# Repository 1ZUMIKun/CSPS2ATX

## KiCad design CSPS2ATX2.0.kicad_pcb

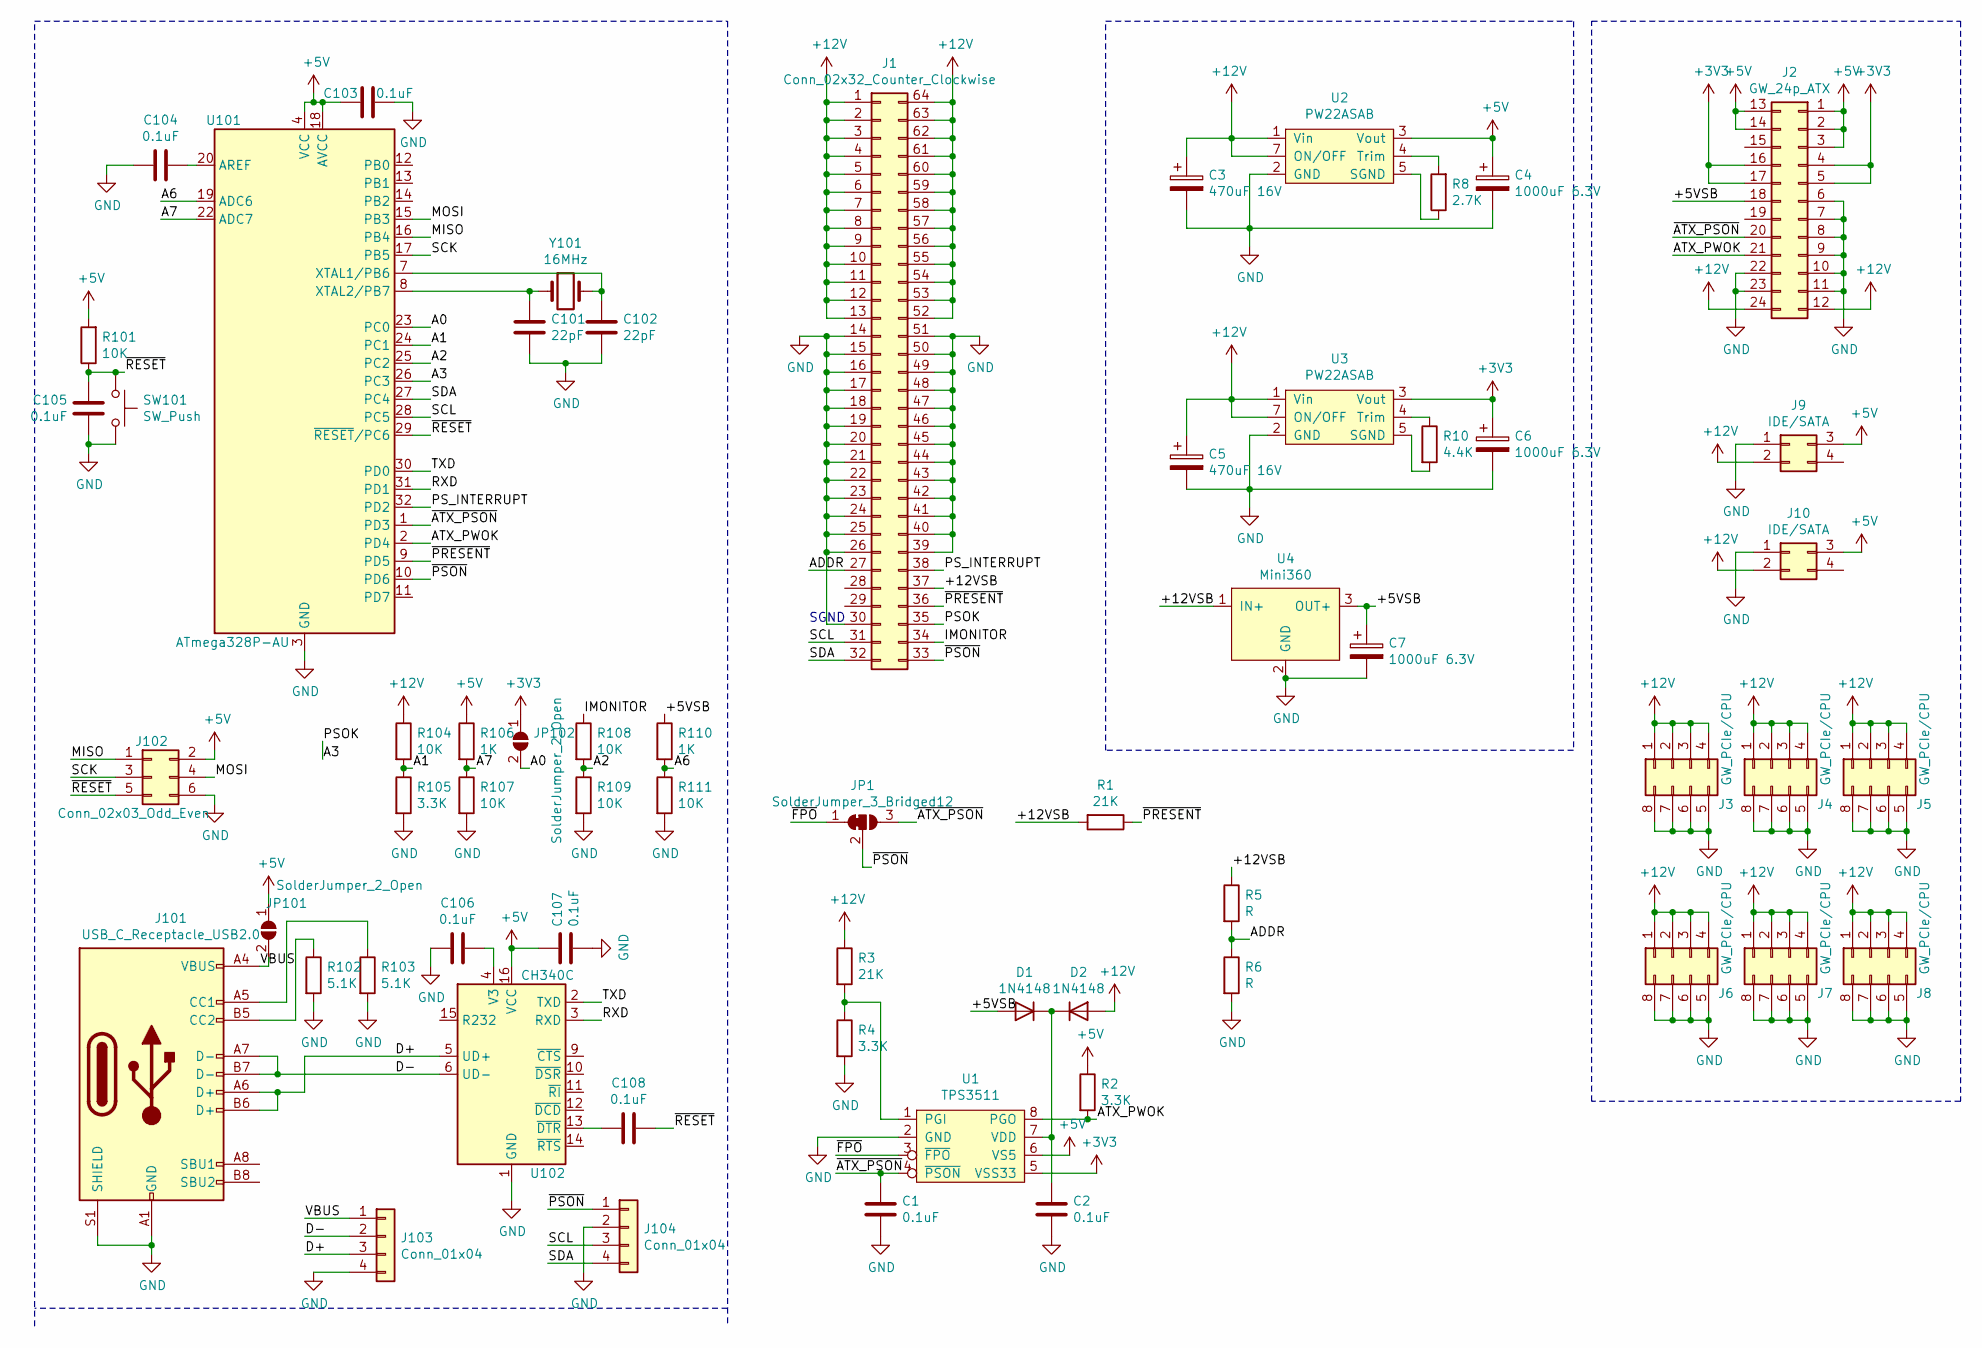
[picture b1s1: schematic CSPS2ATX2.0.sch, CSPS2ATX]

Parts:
C1, C2, C103, C104, C105, C106, C107, C108: 0.1uF; C_0805_2012Metric
C3, C5: 470uF 16V; CP_Elec_8x10
C4, C6, C7: 1000uF 6.3V; CP_Elec_8x10
C101, C102: 22pF; C_0805_2012Metric
D1, D2: 1N4148; D_SOD-523
J1: Conn_02x32_Counter_Clockwise; CSPS_64P_2.54mm
J2: GW_24p_ATX; ATX_24Pin_P4.20mm_Vertical_4.20mm
J3, J4, J5, J6, J7, J8: GW_PCIe/CPU; ATX_8Pin_P4.20mm_Vertical_4.20mm
J9, J10: IDE/SATA; ATX_4Pin_P4.20mm_Vertical_4.20mm
J101: USB_C_Receptacle_USB2.0; USB_C_Receptacle_Palconn_UTC16-G
J102: Conn_02x03_Odd_Even; PinHeader_2x03_P2.54mm_Vertical
J103, J104: Conn_01x04; PinHeader_1x04_P2.54mm_Vertical
JP1: SolderJumper_3_Bridged12; SolderJumper-3_P1.3mm_Bridged12_RoundedPad1.0x1.5mm
JP101, JP102: SolderJumper_2_Open; SolderJumper-2_P1.3mm_Open_RoundedPad1.0x1.5mm
R1, R3: 21K; R_0805_2012Metric
R2, R4, R105: 3.3K; R_0805_2012Metric
R5, R6: R; R_0805_2012Metric
R8: 2.7K; R_0805_2012Metric
R10: 4.4K; R_0805_2012Metric
R101, R104, R107, R108, R109, R111: 10K; R_0805_2012Metric
R102, R103: 5.1K; R_0805_2012Metric
R106, R110: 1K; R_0805_2012Metric
SW101: SW_Push; SW_SPST_FSMSM
U1: TPS3511; SOIC-8_3.9x4.9mm_P1.27mm
U2, U3: PW22ASAB
U4: Mini360
U101: ATmega328P-AU; TQFP-32_7x7mm_P0.8mm
U102: CH340C; SOIC-16_3.9x9.9mm_P1.27mm
Y101: 16MHz; Crystal_SMD_5032-2Pin_5.0x3.2mm

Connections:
+3V3: C6.1, J2.4, J2.5, J2.16, J2.17, JP102.1 (A), U1.5 (VSS33), U3.3 (Vout)
+5V: C4.1, C103.2, C107.1, J2.1, J2.2, J2.3, J2.13, J2.14, J9.3, J10.3, J102.2, JP101.1 (A), R2.1, R101.2, R106.1, U1.6 (VS5), U2.3 (Vout), U101.4 (VCC), U101.6 (VCC), U101.18 (AVCC), U102.16 (VCC)
+12V: C3.1, C5.1, D2.2 (A), J1.1, J1.2, J1.3, J1.4, J1.5, J1.6, J1.7, J1.8, J1.9, J1.10, J1.11, J1.12, J1.13, J1.52, J1.53, J1.54, J1.55, J1.56, J1.57, J1.58, J1.59, J1.60, J1.61, J1.62, J1.63, J1.64, J2.12, J2.24, J3.1, J3.2, J3.3, J3.4, J4.1, J4.2, J4.3, J4.4, J5.1, J5.2, J5.3, J5.4, J6.1, J6.2, J6.3, J6.4, J7.1, J7.2, J7.3, J7.4, J8.1, J8.2, J8.3, J8.4, J9.2, J10.2, R3.1, R104.1, U2.1 (Vin), U2.7 (ON/OFF), U3.1 (Vin), U3.7 (ON/OFF)
/+5VSB: C7.1, D1.2 (A), J2.18, R110.1, U4.3 (OUT+)
/+12VSB: J1.37, R1.2, R5.1, U4.1 (IN+)
/A0: JP102.2 (B), U101.23 (PC0)
/A1: R104.2, R105.1, U101.24 (PC1)
/A2: R108.2, R109.1, U101.25 (PC2)
/A3: J1.35, U101.26 (PC3)
/A6: R110.2, R111.1, U101.19 (ADC6)
/A7: R106.2, R107.1, U101.22 (ADC7)
/ADDR: J1.27, R5.2, R6.1
/ATX_PWOK: J2.21, R2.2, U1.8 (PGO), U101.2 (PD4)
/D+: J101.A6 (D+), J101.B6 (D+), J103.3, U102.5 (UD+)
/D-: J101.A7 (D-), J101.B7 (D-), J103.2, U102.6 (UD-)
/IMONITOR: J1.34, R108.1
/MISO: J102.1, U101.16 (PB4)
/MOSI: J102.4, U101.15 (PB3)
/PS_INTERRUPT: J1.38, U101.32 (PD2)
/RXD: U101.31 (PD1), U102.3 (RXD)
/SCK: J102.3, U101.17 (PB5)
/SCL: J1.31, J104.3, U101.28 (PC5)
/SDA: J1.32, J104.4, U101.27 (PC4)
/TXD: U101.30 (PD0), U102.2 (TXD)
/VBUS: J101.A4 (VBUS), J101.A9 (VBUS), J101.B4 (VBUS), J101.B9 (VBUS), J103.1, JP101.2 (B)
/~ATX_PSON: C1.1, J2.20, JP1.3 (B), U1.4 (~PSON), U101.1 (PD3)
/~FPO: JP1.1 (A), U1.3 (~FPO)
/~PRESENT: J1.36, R1.1, U101.9 (PD5)
/~PSON: J1.33, J104.1, JP1.2 (C), U101.10 (PD6)
/~RESET: C105.2, C108.2, J102.5, R101.1, SW101.1, U101.29 (~RESET~/PC6)
GND: C1.2, C2.2, C3.2, C4.2, C5.2, C6.2, C7.2, C101.2, C102.2, C103.1, C104.1, C105.1, C106.2, C107.2, J1.14, J1.15, J1.16, J1.17, J1.18, J1.19, J1.20, J1.21, J1.22, J1.23, J1.24, J1.25, J1.26, J1.30, J1.39, J1.40, J1.41, J1.42, J1.43, J1.44, J1.45, J1.46, J1.47, J1.48, J1.49, J1.50, J1.51, J2.6, J2.7, J2.8, J2.9, J2.10, J2.11, J2.22, J2.23, J3.5, J3.6, J3.7, J3.8, J4.5, J4.6, J4.7, J4.8, J5.5, J5.6, J5.7, J5.8, J6.5, J6.6, J6.7, J6.8, J7.5, J7.6, J7.7, J7.8, J8.5, J8.6, J8.7, J8.8, J9.1, J10.1, J101.A1 (GND), J101.A12 (GND), J101.B1 (GND), J101.B12 (GND), J101.S1 (SHIELD), J102.6, J103.4, J104.2, R4.2, R6.2, R102.2, R103.2, R105.2, R107.2, R109.2, R111.2, SW101.2, U1.2 (GND), U2.2 (GND), U3.2 (GND), U4.2 (GND), U101.3 (GND), U101.5 (GND), U101.21 (GND), U102.1 (GND)
unnamed: C2.1, D1.1 (K), D2.1 (K), U1.7 (VDD)
unnamed: C101.1, U101.8 (XTAL2/PB7), Y101.1
unnamed: C102.1, U101.7 (XTAL1/PB6), Y101.2
unnamed: C104.2, U101.20 (AREF)
unnamed: C106.1, U102.4 (V3)
unnamed: C108.1, U102.13 (~DTR)
unnamed: J101.A5 (CC1), R103.1
unnamed: J101.B5 (CC2), R102.1
unnamed: R3.2, R4.1, U1.1 (PGI)
unnamed: R8.1, U2.5 (SGND)
unnamed: R8.2, U2.4 (Trim)
unnamed: R10.1, U3.4 (Trim)
unnamed: R10.2, U3.5 (SGND)

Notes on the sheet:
SGND

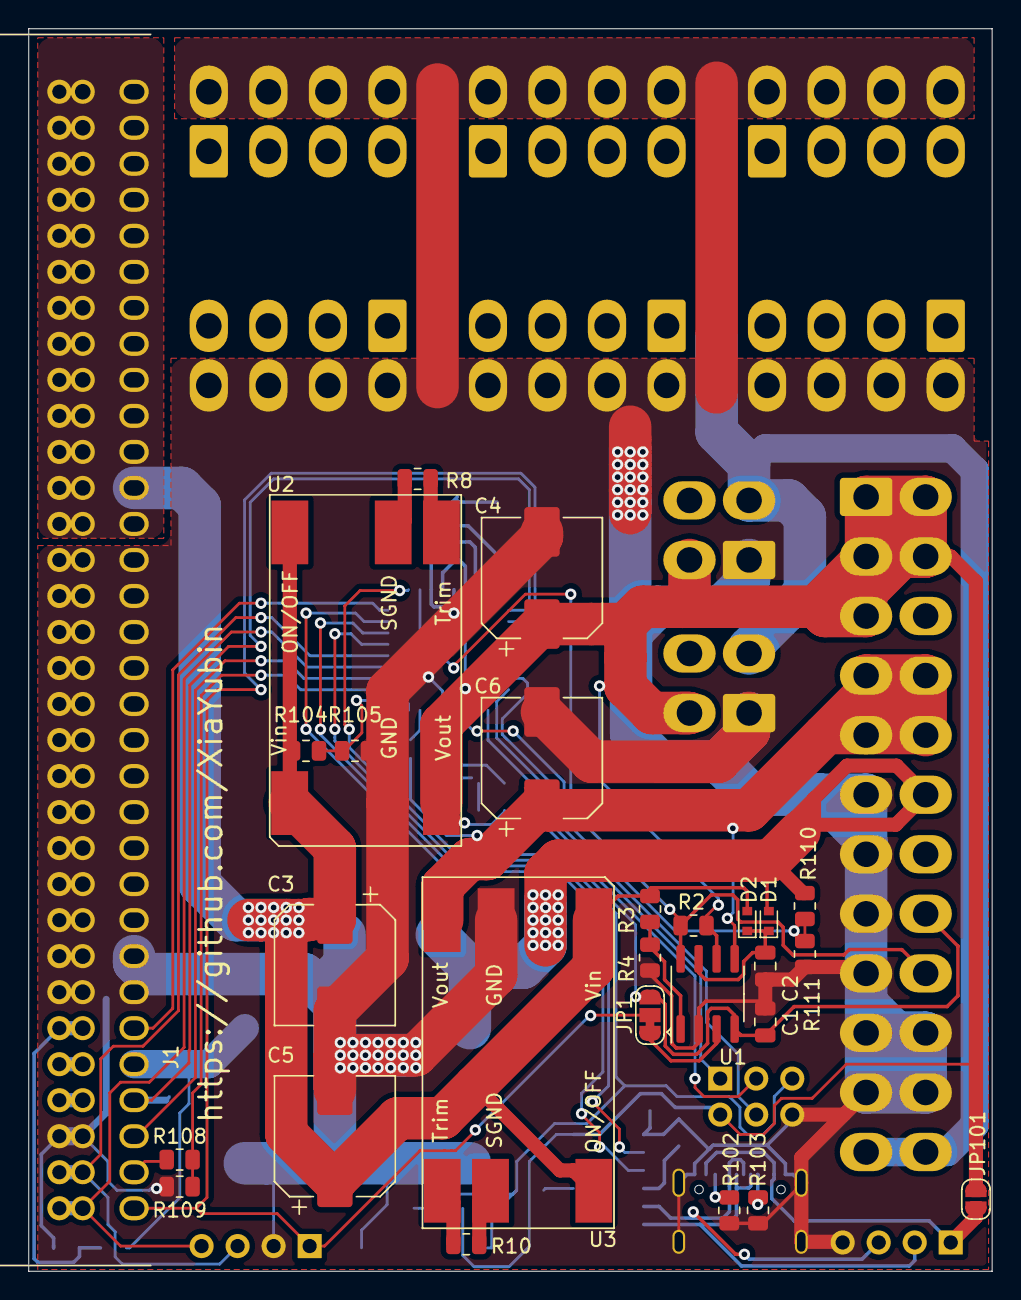
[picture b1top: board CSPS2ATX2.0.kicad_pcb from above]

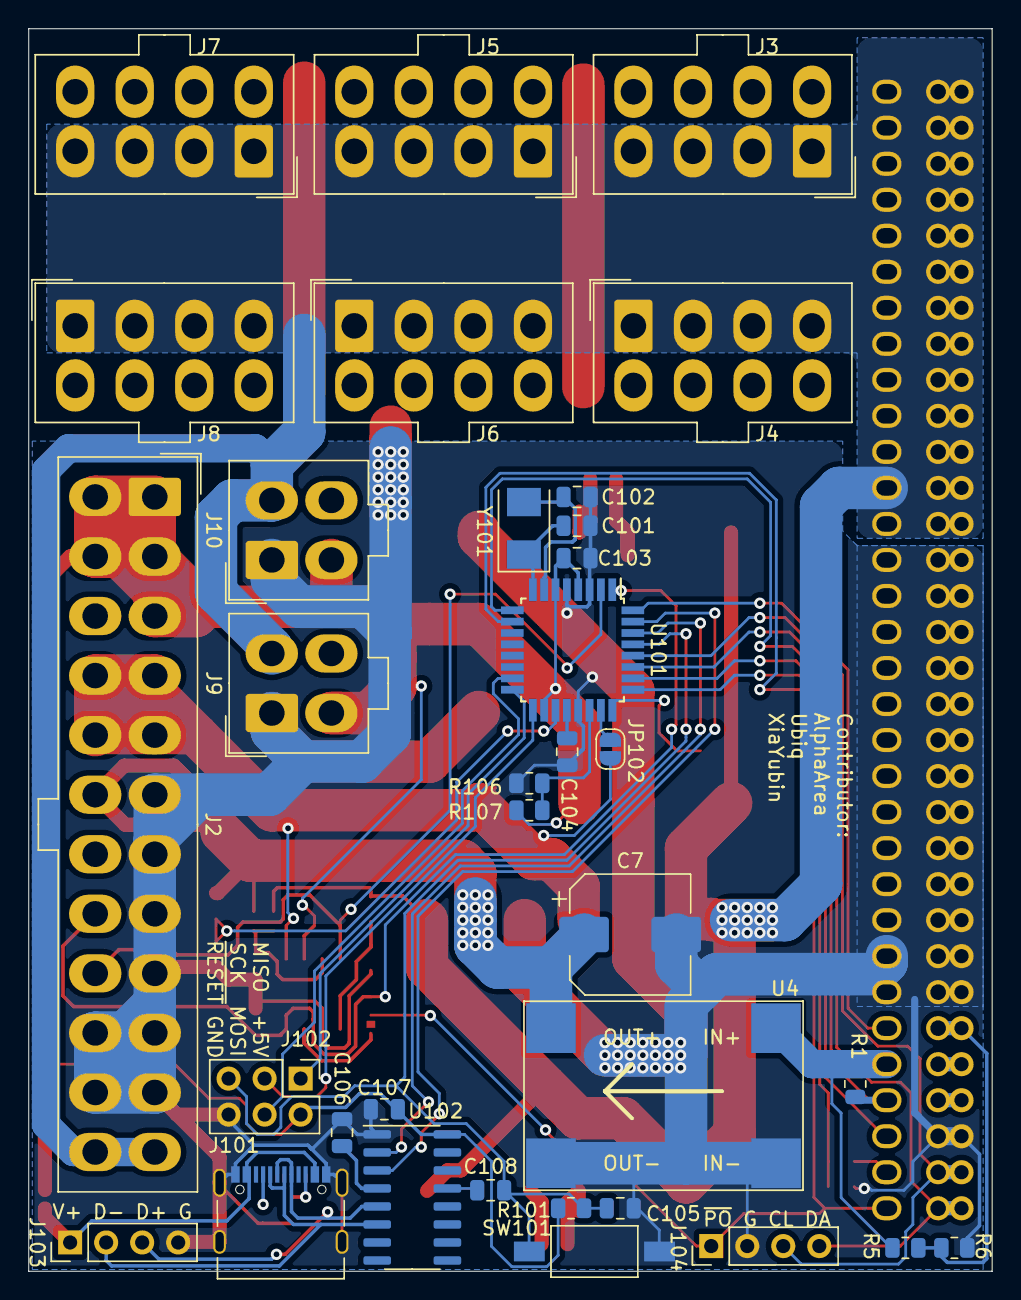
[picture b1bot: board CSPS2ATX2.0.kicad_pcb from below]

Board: 2 copper layers, 67.9 x 87.6 mm, 61 parts (34 on the bottom side), 44 nets.

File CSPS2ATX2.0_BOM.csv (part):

Source:,D:\Files\DPS1200W\CSPS2ATX2.0h\CSPS2ATX2.0.sch,,,,,
Date:,2021/4/16 0:27,,,,,
Tool:,Eeschema (5.1.9)-1,,,,,
Generator:,C:\Program Files\KiCad\bin\scripting\plugins/bom_csv_grouped_by_value.py,,,,,
Component Count:,63,,,,,
,,,,,,
Individual Components:,,,,,,
,,,,,,
Item,Qty,Reference(s),Value,LibPart,Footprint,Datasheet
,,C1,0.1uF,Device:C,Capacitor_SMD:C_0805_2012Metric,~
,,C2,0.1uF,Device:C,Capacitor_SMD:C_0805_2012Metric,~
,,C3,470uF 16V,Device:CP,Capacitor_SMD:CP_Elec_8x10,~
,,C4,1000uF 6.3V,Device:CP,Capacitor_SMD:CP_Elec_8x10,~
,,C5,470uF 16V,Device:CP,Capacitor_SMD:CP_Elec_8x10,~
,,C6,1000uF 6.3V,Device:CP,Capacitor_SMD:CP_Elec_8x10,~
,,C7,1000uF 6.3V,Device:CP,Capacitor_SMD:CP_Elec_8x10,~
,,C101,22pF,Device:C,Capacitor_SMD:C_0805_2012Metric,~
,,C102,22pF,Device:C,Capacitor_SMD:C_0805_2012Metric,~
,,C103,0.1uF,Device:C,Capacitor_SMD:C_0805_2012Metric,~
,,C104,0.1uF,Device:C,Capacitor_SMD:C_0805_2012Metric,~
,,C105,0.1uF,Device:C,Capacitor_SMD:C_0805_2012Metric,~
,,C106,0.1uF,Device:C,Capacitor_SMD:C_0805_2012Metric,~
,,C107,0.1uF,Device:C,Capacitor_SMD:C_0805_2012Metric,~
,,C108,0.1uF,Device:C,Capacitor_SMD:C_0805_2012Metric,~
,,D1,1N4148,Device:D,Diode_SMD:D_SOD-523,~
,,D2,1N4148,Device:D,Diode_SMD:D_SOD-523,~
,,J1,Conn_02x32_Counter_Clockwise,Connector_Generic:Conn_02x32_Counter_Clockwise,KCORES_Connector_CSPS:CSPS_64P_2.54mm,~
,,J2,GW_24p_ATX,Connector_Generic:Conn_02x12_Top_Bottom,KCORES_Connector_ATX_Power:ATX_24Pin_P4.20mm_Vertical_4.20mm,~
,,J3,GW_PCIe/CPU,Connector_Generic:Conn_02x04_Counter_Clockwise,KCORES_Connector_ATX_Power:ATX_8Pin_P4.20mm_Vertical_4.20mm,~
,,J4,GW_PCIe/CPU,Connector_Generic:Conn_02x04_Counter_Clockwise,KCORES_Connector_ATX_Power:ATX_8Pin_P4.20mm_Vertical_4.20mm,~
,,J5,GW_PCIe/CPU,Connector_Generic:Conn_02x04_Counter_Clockwise,KCORES_Connector_ATX_Power:ATX_8Pin_P4.20mm_Vertical_4.20mm,~
,,J6,GW_PCIe/CPU,Connector_Generic:Conn_02x04_Counter_Clockwise,KCORES_Connector_ATX_Power:ATX_8Pin_P4.20mm_Vertical_4.20mm,~
,,J7,GW_PCIe/CPU,Connector_Generic:Conn_02x04_Counter_Clockwise,KCORES_Connector_ATX_Power:ATX_8Pin_P4.20mm_Vertical_4.20mm,~
,,J8,GW_PCIe/CPU,Connector_Generic:Conn_02x04_Counter_Clockwise,KCORES_Connector_ATX_Power:ATX_8Pin_P4.20mm_Vertical_4.20mm,~
,,J9,IDE/SATA,Connector_Generic:Conn_02x02_Top_Bottom,KCORES_Connector_ATX_Power:ATX_4Pin_P4.20mm_Vertical_4.20mm,~
,,J10,IDE/SATA,Connector_Generic:Conn_02x02_Top_Bottom,KCORES_Connector_ATX_Power:ATX_4Pin_P4.20mm_Vertical_4.20mm,~
,,J101,USB_C_Receptacle_USB2.0,Connector:USB_C_Receptacle_USB2.0,Connector_USB:USB_C_Receptacle_Palconn_UTC16-G,https://www.usb.org/sites/default/files/documents/usb_type-c.zip
,,J102,Conn_02x03_Odd_Even,Connector_Generic:Conn_02x03_Odd_Even,Connector_PinHeader_2.54mm:PinHeader_2x03_P2.54mm_Vertical,~
,,J103,Conn_01x04,Connector_Generic:Conn_01x04,Connector_PinHeader_2.54mm:PinHeader_1x04_P2.54mm_Vertical,~
,,J104,Conn_01x04,Connector_Generic:Conn_01x04,Connector_PinHeader_2.54mm:PinHeader_1x04_P2.54mm_Vertical,~
,,JP1,SolderJumper_3_Bridged12,Jumper:SolderJumper_3_Bridged12,Jumper:SolderJumper-3_P1.3mm_Bridged12_RoundedPad1.0x1.5mm,~
,,JP101,SolderJumper_2_Open,Jumper:SolderJumper_2_Open,Jumper:SolderJumper-2_P1.3mm_Open_RoundedPad1.0x1.5mm,~
,,JP102,SolderJumper_2_Open,Jumper:SolderJumper_2_Open,Jumper:SolderJumper-2_P1.3mm_Open_RoundedPad1.0x1.5mm,~
,,R1,21K,Device:R,Resistor_SMD:R_0805_2012Metric,~
,,R2,3.3K,Device:R,Resistor_SMD:R_0805_2012Metric,~
,,R3,21K,Device:R,Resistor_SMD:R_0805_2012Metric,~
,,R4,3.3K,Device:R,Resistor_SMD:R_0805_2012Metric,~
,,R5,R,Device:R,Resistor_SMD:R_0805_2012Metric,~
,,R6,R,Device:R,Resistor_SMD:R_0805_2012Metric,~
,,R7,R,Device:R,Resistor_SMD:R_0805_2012Metric,~
,,R8,2.7K,Device:R,Resistor_SMD:R_0805_2012Metric,~
,,R9,R,Device:R,Resistor_SMD:R_0805_2012Metric,~
,,R10,4.4K,Device:R,Resistor_SMD:R_0805_2012Metric,~
,,R101,10K,Device:R,Resistor_SMD:R_0805_2012Metric,~
,,R102,5.1K,Device:R,Resistor_SMD:R_0805_2012Metric,~
,,R103,5.1K,Device:R,Resistor_SMD:R_0805_2012Metric,~
,,R104,10K,Device:R,Resistor_SMD:R_0805_2012Metric,~
,,R105,3.3K,Device:R,Resistor_SMD:R_0805_2012Metric,~
,,R106,1K,Device:R,Resistor_SMD:R_0805_2012Metric,~
,,R107,10K,Device:R,Resistor_SMD:R_0805_2012Metric,~
,,R108,10K,Device:R,Resistor_SMD:R_0805_2012Metric,~
,,R109,10K,Device:R,Resistor_SMD:R_0805_2012Metric,~
,,R110,1K,Device:R,Resistor_SMD:R_0805_2012Metric,~
,,R111,10K,Device:R,Resistor_SMD:R_0805_2012Metric,~
,,SW101,SW_Push,Switch:SW_Push,Button_Switch_SMD:SW_SPST_FSMSM,~
,,U1,TPS3511,KCORES_Power_Supervisor:TPS3511,Package_SO:SOIC-8_3.9x4.9mm_P1.27mm,
,,U2,PW22ASAB,KCORES_Converter_DCDC:PW22ASAB,KCORES_Converter_DCDC:PW22ASAB,
,,U3,PW22ASAB,KCORES_Converter_DCDC:PW22ASAB,KCORES_Converter_DCDC:PW22ASAB,
,,U4,Mini360,KCORES_Converter_DCDC:Mini360,KCORES_Converter_DCDC:Mini360,
,,U101,ATmega328P-AU,MCU_Microchip_ATmega:ATmega328P-AU,Package_QFP:TQFP-32_7x7mm_P0.8mm,http://ww1.microchip.com/downloads/en/DeviceDoc/ATmega328_P%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
,,U102,CH340C,Interface_USB:CH340C,Package_SO:SOIC-16_3.9x9.9mm_P1.27mm,https://datasheet.lcsc.com/szlcsc/Jiangsu-Qin-Heng-CH340C_C8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
,,Y101,16MHz,Device:Crystal,Crystal:Crystal_SMD_5032-2Pin_5.0x3.2mm,~
,,,,,,
,,,,,,
,,,,,,
Collated Components:,,,,,,
,,,,,,
Item,Qty,Reference(s),Value,LibPart,Footprint,Datasheet
1,8,"C1, C2, C103, C104, C105, C106, C107, C108",0.1uF,Device:C,Capacitor_SMD:C_0805_2012Metric,~
2,2,"C3, C5",470uF 16V,Device:CP,Capacitor_SMD:CP_Elec_8x10,~
3,3,"C4, C6, C7",1000uF 6.3V,Device:CP,Capacitor_SMD:CP_Elec_8x10,~
4,2,"C101, C102",22pF,Device:C,Capacitor_SMD:C_0805_2012Metric,~
5,2,"D1, D2",1N4148,Device:D,Diode_SMD:D_SOD-523,~
6,1,J1,Conn_02x32_Counter_Clockwise,Connector_Generic:Conn_02x32_Counter_Clockwise,KCORES_Connector_CSPS:CSPS_64P_2.54mm,~
7,1,J2,GW_24p_ATX,Connector_Generic:Conn_02x12_Top_Bottom,KCORES_Connector_ATX_Power:ATX_24Pin_P4.20mm_Vertical_4.20mm,~
8,6,"J3, J4, J5, J6, J7, J8",GW_PCIe/CPU,Connector_Generic:Conn_02x04_Counter_Clockwise,KCORES_Connector_ATX_Power:ATX_8Pin_P4.20mm_Vertical_4.20mm,~
9,2,"J9, J10",IDE/SATA,Connector_Generic:Conn_02x02_Top_Bottom,KCORES_Connector_ATX_Power:ATX_4Pin_P4.20mm_Vertical_4.20mm,~
10,1,J101,USB_C_Receptacle_USB2.0,Connector:USB_C_Receptacle_USB2.0,Connector_USB:USB_C_Receptacle_Palconn_UTC16-G,https://www.usb.org/sites/default/files/documents/usb_type-c.zip
11,1,J102,Conn_02x03_Odd_Even,Connector_Generic:Conn_02x03_Odd_Even,Connector_PinHeader_2.54mm:PinHeader_2x03_P2.54mm_Vertical,~
12,2,"J103, J104",Conn_01x04,Connector_Generic:Conn_01x04,Connector_PinHeader_2.54mm:PinHeader_1x04_P2.54mm_Vertical,~
13,1,JP1,SolderJumper_3_Bridged12,Jumper:SolderJumper_3_Bridged12,Jumper:SolderJumper-3_P1.3mm_Bridged12_RoundedPad1.0x1.5mm,~
14,2,"JP101, JP102",SolderJumper_2_Open,Jumper:SolderJumper_2_Open,Jumper:SolderJumper-2_P1.3mm_Open_RoundedPad1.0x1.5mm,~
15,2,"R1, R3",21K,Device:R,Resistor_SMD:R_0805_2012Metric,~
16,3,"R2, R4, R105",3.3K,Device:R,Resistor_SMD:R_0805_2012Metric,~
17,4,"R5, R6, R7, R9",R,Device:R,Resistor_SMD:R_0805_2012Metric,~
18,1,R8,2.7K,Device:R,Resistor_SMD:R_0805_2012Metric,~
19,1,R10,4.4K,Device:R,Resistor_SMD:R_0805_2012Metric,~
20,6,"R101, R104, R107, R108, R109, R111",10K,Device:R,Resistor_SMD:R_0805_2012Metric,~
21,2,"R102, R103",5.1K,Device:R,Resistor_SMD:R_0805_2012Metric,~
22,2,"R106, R110",1K,Device:R,Resistor_SMD:R_0805_2012Metric,~
23,1,SW101,SW_Push,Switch:SW_Push,Button_Switch_SMD:SW_SPST_FSMSM,~
24,1,U1,TPS3511,KCORES_Power_Supervisor:TPS3511,Package_SO:SOIC-8_3.9x4.9mm_P1.27mm,
25,2,"U2, U3",PW22ASAB,KCORES_Converter_DCDC:PW22ASAB,KCORES_Converter_DCDC:PW22ASAB,
26,1,U4,Mini360,KCORES_Converter_DCDC:Mini360,KCORES_Converter_DCDC:Mini360,
27,1,U101,ATmega328P-AU,MCU_Microchip_ATmega:ATmega328P-AU,Package_QFP:TQFP-32_7x7mm_P0.8mm,http://ww1.microchip.com/downloads/en/DeviceDoc/ATmega328_P%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
28,1,U102,CH340C,Interface_USB:CH340C,Package_SO:SOIC-16_3.9x9.9mm_P1.27mm,https://datasheet.lcsc.com/szlcsc/Jiangsu-Qin-Heng-CH340C_C8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

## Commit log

2021-04-10 Create
2021-04-15 confirm trim resistor
2021-04-20 remove R7 R9
